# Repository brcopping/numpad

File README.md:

# numpad PCB

I am following MrKeeb's and Gondolindrin's video series [PCB from Scratch with Gondo](https://youtu.be/Nk0egpDFqRA) and [ai03's guides](https://wiki.ai03.me/) to create my own numpad.

The layout is a standard numpad which can be seen here on [keyboard layout editor](http://www.keyboard-layout-editor.com/#/gists/febd745a52b943ce2c9e8b8bd37d3d38)

I created a rough case design ([main body](https://www.tinkercad.com/things/3bGqK5EBuhx) & [high profile rim](https://www.tinkercad.com/things/5EjXz9Ort4S)) for this PCB on tinkercad, it will take a [lazercut metal plate](https://github.com/brcopping/numpad/blob/master/Swill-Switch-Layer.dxf) for switch mounting. 

To hold the case together I used M3 nuts and bolts, 35mm for the back and 25mm for the front (all 4 protrude too much, so probably 33mm and 22mm would be better if attainable. Will cut mine down when i get a chance)

Numpad firmware added to [my QMK fork on git](https://github.com/brcopping/qmk_firmware). To genreate the firmware file run:
`make handwired/ben18:default`

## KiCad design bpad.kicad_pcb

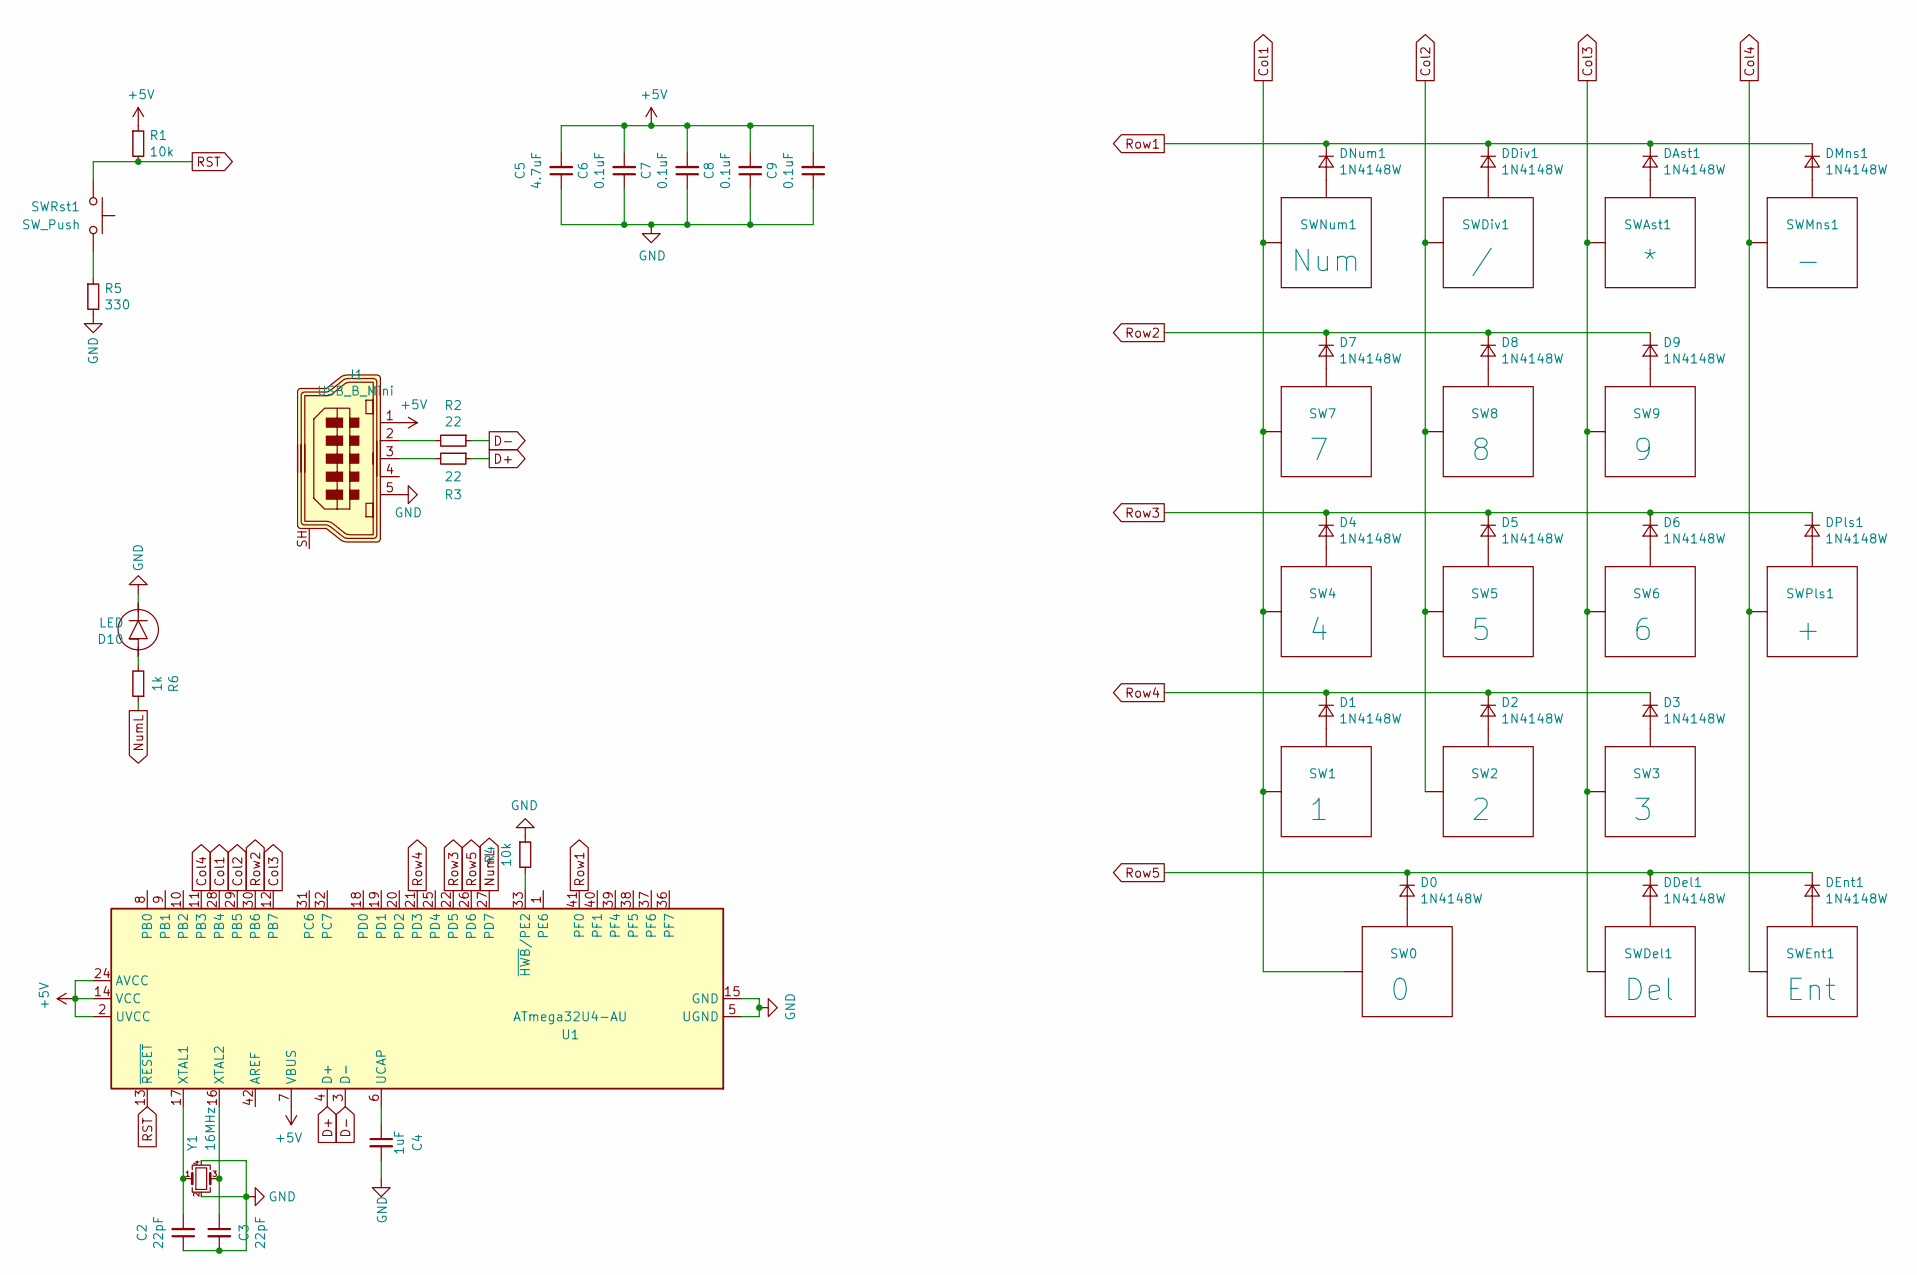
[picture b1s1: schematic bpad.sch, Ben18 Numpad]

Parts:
C2, C3: 22pF; C_0603_1608Metric_Pad1.05x0.95mm_HandSolder
C4: 1uF; C_0603_1608Metric_Pad1.05x0.95mm_HandSolder
C5: 4.7uF; C_0805_2012Metric_Pad1.15x1.40mm_HandSolder
C6, C7, C8, C9: 0.1uF; C_0603_1608Metric_Pad1.05x0.95mm_HandSolder
D0, D1, D2, D3, D4, D5, D6, D7, D8, D9: 1N4148W; D_SOD-323_HandSoldering
D10: LED; LED_THT_2.54mm
DAst1: 1N4148W; D_SOD-323_HandSoldering
DDel1: 1N4148W; D_SOD-323_HandSoldering
DDiv1: 1N4148W; D_SOD-323_HandSoldering
DEnt1: 1N4148W; D_SOD-323_HandSoldering
DMns1: 1N4148W; D_SOD-323_HandSoldering
DNum1: 1N4148W; D_SOD-323_HandSoldering
DPls1: 1N4148W; D_SOD-323_HandSoldering
J1: USB_B_Mini; USB_Mini_B_Female_548190519_top
R1, R4: 10k; R_0603_1608Metric_Pad1.05x0.95mm_HandSolder
R2, R3: 22; R_0603_1608Metric_Pad1.05x0.95mm_HandSolder
R5: 330; R_0603_1608Metric_Pad1.05x0.95mm_HandSolder
R6: 1k; R_0603_1608Metric_Pad1.05x0.95mm_HandSolder
SW0: 0; MX200R
SW1: 1; MX100
SW2: 2; MX100
SW3: 3; MX100
SW4: 4; MX100
SW5: 5; MX100
SW6: 6; MX100
SW7: 7; MX100
SW8: 8; MX100
SW9: 9; MX100
SWAst1: *; MX100
SWDel1: Del; MX100
SWDiv1: /; MX100
SWEnt1: Ent; MX200
SWMns1: -; MX100
SWNum1: Num; MX100
SWPls1: +; MX200
SWRst1: SW_Push; smdPushBtn
U1: ATmega32U4-AU; TQFP-44_10x10mm_P0.8mm
Y1: 16MHz; Crystal_SMD_3225-4Pin_3.2x2.5mm_HandSoldering

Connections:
+5V: C5.2, C6.2, C7.2, C8.2, C9.2, J1.1, R1.1, U1.2 (UVCC), U1.7 (VBUS), U1.14 (VCC), U1.24 (AVCC), U1.34 (VCC), U1.44 (AVCC)
Col1: SW0.1 (Col), SW1.1 (Col), SW4.1 (Col), SW7.1 (Col), SWNum1.1 (Col), U1.28 (PB4)
Col2: SW2.1 (Col), SW5.1 (Col), SW8.1 (Col), SWDiv1.1 (Col), U1.29 (PB5)
Col3: SW3.1 (Col), SW6.1 (Col), SW9.1 (Col), SWAst1.1 (Col), SWDel1.1 (Col), U1.12 (PB7)
Col4: SWEnt1.1 (Col), SWMns1.1 (Col), SWPls1.1 (Col), U1.11 (PB3)
D+: R3.1, U1.4 (D+)
D-: R2.1, U1.3 (D-)
GND: C2.1, C3.2, C4.2, C5.1, C6.1, C7.1, C8.1, C9.1, D10.K, J1.5, R4.1, R5.2, U1.5 (UGND), U1.15 (GND), U1.23 (GND), U1.35 (GND), U1.43 (GND), Y1.2, Y1.4
unnamed: C2.2, U1.17 (XTAL1), Y1.1
unnamed: C3.1, U1.16 (XTAL2), Y1.3
unnamed: C4.1, U1.6 (UCAP)
unnamed: D0.2 (A), SW0.2 (Row)
unnamed: D1.2 (A), SW1.2 (Row)
unnamed: D2.2 (A), SW2.2 (Row)
unnamed: D3.2 (A), SW3.2 (Row)
unnamed: D4.2 (A), SW4.2 (Row)
unnamed: D5.2 (A), SW5.2 (Row)
unnamed: D6.2 (A), SW6.2 (Row)
unnamed: D7.2 (A), SW7.2 (Row)
unnamed: D8.2 (A), SW8.2 (Row)
unnamed: D9.2 (A), SW9.2 (Row)
unnamed: D10.A, R6.2
unnamed: DAst1.2 (A), SWAst1.2 (Row)
unnamed 23: DDel1.2 (A), SWDel1.2 (Row); also elsewhere on the board
unnamed: DDiv1.2 (A), SWDiv1.2 (Row)
unnamed 25: DEnt1.2 (A), SWEnt1.2 (Row); also elsewhere on the board
unnamed: DMns1.2 (A), SWMns1.2 (Row)
unnamed: DNum1.2 (A), SWNum1.2 (Row)
unnamed 28: DPls1.2 (A), SWPls1.2 (Row); also elsewhere on the board
unnamed: J1.2, R2.2
unnamed: J1.3, R3.2
unnamed: R4.2, U1.33 (~HWB~/PE2)
unnamed: R5.1, SWRst1.2
NumL: R6.1, U1.27 (PD7)
RST: R1.2, SWRst1.1, U1.13 (~RESET)
Row1: DAst1.1 (K), DDiv1.1 (K), DMns1.1 (K), DNum1.1 (K), U1.41 (PF0)
Row2: D7.1 (K), D8.1 (K), D9.1 (K), U1.30 (PB6)
Row3: D4.1 (K), D5.1 (K), D6.1 (K), DPls1.1 (K), U1.22 (PD5); also elsewhere on the board
Row4: D1.1 (K), D2.1 (K), D3.1 (K), U1.21 (PD3)
Row5: D0.1 (K), DDel1.1 (K), DEnt1.1 (K), U1.26 (PD6); also elsewhere on the board

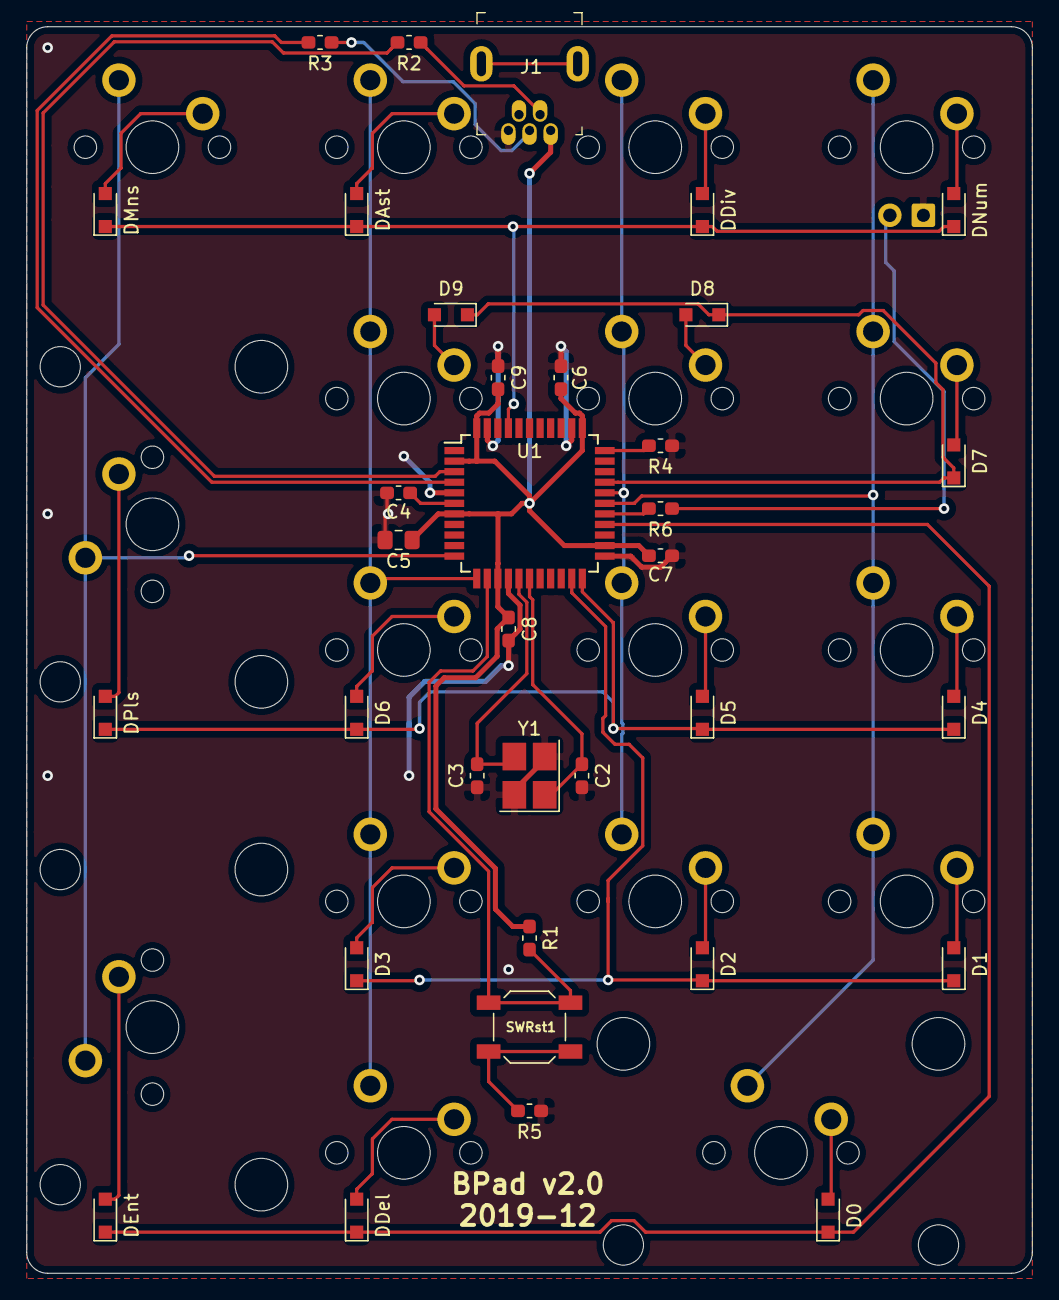
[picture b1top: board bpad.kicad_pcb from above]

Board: 2 copper layers, 76.2 x 94.5 mm, 53 parts (0 on the bottom side), 40 nets.

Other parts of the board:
DDel: 1N4148W; D_SOD-323_HandSoldering
DEnt: 1N4148W; D_SOD-323_HandSoldering
DPls: 1N4148W; D_SOD-323_HandSoldering

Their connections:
unnamed 23: DDel.2; also elsewhere on the board
unnamed 25: DEnt.2; also elsewhere on the board
unnamed 28: DPls.2; also elsewhere on the board
Row3: DPls.1; also elsewhere on the board
Row5: DDel.1, DEnt.1; also elsewhere on the board

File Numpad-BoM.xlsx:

C2 C3 | 2 | 22pF | Capacitor_SMD:C_0603_1608Metric_Pad1.05x0.95mm_HandSolder |  | https://www.digikey.co.uk/product-detail/en/avx-corporation/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
C4 | 1 | 1uF | Capacitor_SMD:C_0603_1608Metric_Pad1.05x0.95mm_HandSolder |  | https://www.digikey.co.uk/product-detail/en/CC0805JKX7R9BB10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 | 805
C5 | 1 | 4.7uF | Capacitor_SMD:C_0603_1608Metric_Pad1.05x0.95mm_HandSolder |  | https://www.digikey.co.uk/product-detail/en/samsung-electro-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 | 805
C1 C8 C7 C6 C9 | 5 | 0.1uF | Capacitor_SMD:C_0603_1608Metric_Pad1.05x0.95mm_HandSolder |  | https://www.digikey.co.uk/product-detail/en/CL10B104JB8NNNC/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
DNum1 DDiv1 DAst1 D7 D8 D9 D4 D5 D6 D1 D2 D3 DEnt1 DDel1 D0 DMns1 DPls1 DMns2 | 18 | 1N4148W | Diode_SMD:D_SOD-323_HandSoldering |  | https://www.digikey.co.uk/product-detail/en/1N4148WX-TP/1N41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
J1 | 1 | USB_B_Mini | digikey-kicad-library:USB_Mini_B_Female_548190519 |  | https://www.digikey.co.uk/product-detail/en/molex/0548190519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
R1 R4 | 2 | 10k | Resistor_SMD:R_0603_1608Metric_Pad1.05x0.95mm_HandSolder |  | https://www.digikey.co.uk/product-detail/en/rohm-semiconduct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
R2 R3 | 2 | 22 | Resistor_SMD:R_0603_1608Metric_Pad1.05x0.95mm_HandSolder |  | https://www.digikey.co.uk/product-detail/en/vishay-dale/CRCW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
R5 | 1 | 330 | Resistor_SMD:R_0603_1608Metric_Pad1.05x0.95mm_HandSolder |  | https://www.digikey.co.uk/product-detail/en/yageo/RC0603FR-0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
SW0 | 1 | 0 | AcheronMX:MX200R
SW1 | 1 | 1 | AcheronMX:MX100
SW2 | 1 | 2 | AcheronMX:MX100
SW3 | 1 | 3 | AcheronMX:MX100
SW4 | 1 | 4 | AcheronMX:MX100
SW5 | 1 | 5 | AcheronMX:MX100
SW6 | 1 | 6 | AcheronMX:MX100
SW7 | 1 | 7 | AcheronMX:MX100
SW8 | 1 | 8 | AcheronMX:MX100
SW9 | 1 | 9 | AcheronMX:MX100
SWAst1 | 1 | * | AcheronMX:MX100
SWDel1 | 1 | Del | AcheronMX:MX100
SWDiv1 | 1 | / | AcheronMX:MX100
SWEnt1 | 1 | Ent | AcheronMX:MX200VR
SWMns1 | 1 | -/Bsp | AcheronMX:MX100
SWMns2 | 1 | - | AcheronMX:MX100
SWNum1 | 1 | Num | AcheronMX:MX100
SWPls1 | 1 | + | AcheronMX:MX200VR
SWPls2 | 1 | + | AcheronMX:MX100
SWRst1 | 1 | SW_Push | AcheronHardware:smdPushBtn |  | https://www.digikey.co.uk/product-detail/en/PTS525SM15SMTR2+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
U1 | 1 | ATmega32U4-AU | Package_QFP:TQFP-44_10x10mm_P0.8mm
Y1 | 1 | 16MHz | Crystal:Crystal_SMD_3225-4Pin_3.2x2.5mm_HandSoldering |  | https://www.digikey.co.uk/product-detail/en/ndk-america-inc/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

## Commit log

2019-09-07 numpad pcb design
2019-09-10 Components roughly placed in grid, connected rows and cols to processor
2019-09-13 components roughly placed
2019-09-14 ignore bak files, went bak to standard pcb orientation
2019-09-14 git ignore copied from https://github.com/github/gitignore/blob/master/KiCad.gitignore
2019-09-14 MX labels updated, missed diode spec
2019-09-14 rotated stabiliser holes for tighter pcb
2019-09-19 copied aio3's capacitor settings and fuse placement
2019-09-19 numpad name ben17
2019-09-20 moved some components around
2019-09-22 plate files added, moved around some more components
2019-10-02 added some traces, changed plate file
2019-10-06 placed clock
2019-10-13 allowed split + key
2019-10-15 all componentes withing the confines of the board now, still need to add ground. Not shure about the components around reset button or c5 & c9's grounding
2019-10-15 we can now have a maxiumum of 18 keys, so renamed it Ben18 from Ben17
2019-10-19 ground planes in, thinking about ordering
2019-10-19 two of the capacitors needed larger footprints, have added BoM
2019-10-26 Rotated Pls & Rtn switches, they are loose in the plate in original orientation
2019-11-06 ignore gerbers folder
2019-11-07 I hadnt connected the VBUS, changed it back to 17 keys no option for split plus.
2019-11-30 started again on the layout
2019-12-09 moved the usb around and added label
2019-12-20 ordered v2
2020-03-08 added image of working numpad
2020-03-08 added image of nupad pcb
